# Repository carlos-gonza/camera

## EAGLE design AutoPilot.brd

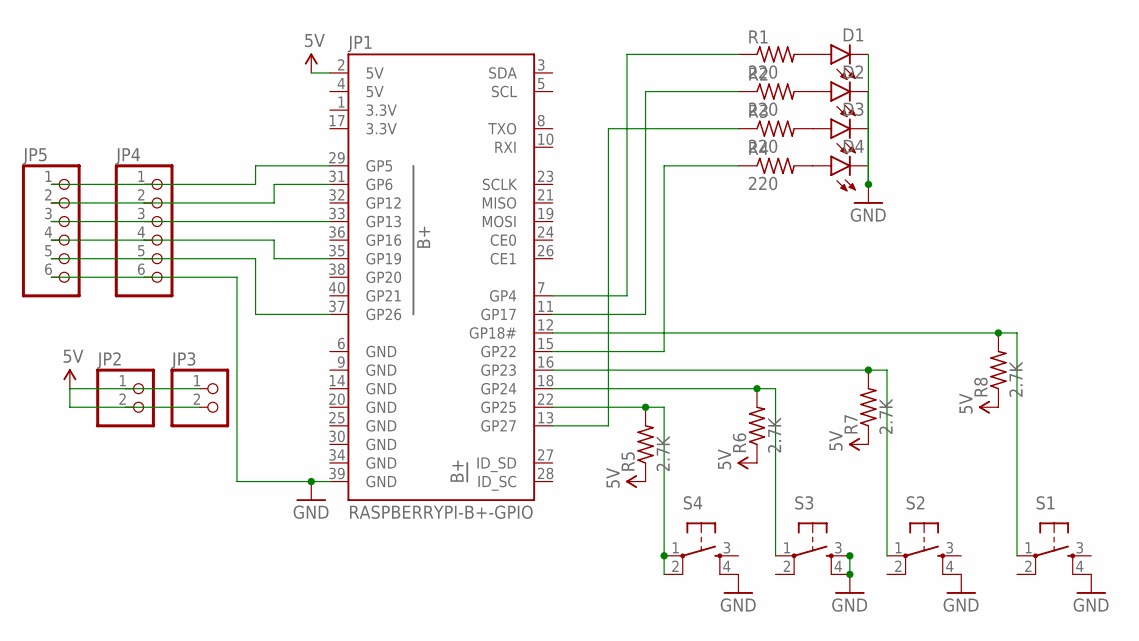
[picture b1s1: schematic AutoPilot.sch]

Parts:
D1, D2, D3, D4: LED5MM
JP1: RASPBERRYPI-B+-GPIO; 2X20-SHROUDED
JP2, JP3: PINHD-1X2; 1X02
JP4, JP5: PINHD-1X6; 1X06
R1, R2, R3, R4: 220; 0204V
R5, R6, R7, R8: 2.7K; 0204V
S1, S2, S3, S4: TAC_SWITCHPTH; TACTILE-PTH

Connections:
3.3V: JP1.1 (3.3V), JP1.17 (3.3V)
5V: JP1.2 (5V), JP1.4 (5V), JP2.1, JP2.2, JP3.1, JP3.2, R5.1, R6.1, R7.1, R8.1
GND: D1.K (C), D2.K (C), D3.K (C), D4.K (C), JP1.6 (GND), JP1.9 (GND), JP1.14 (GND), JP1.20 (GND), JP1.25 (GND), JP1.30 (GND), JP1.34 (GND), JP1.39 (GND), JP4.6, JP5.6, S1.4, S2.4, S3.3, S3.4, S4.4
unnamed: JP1.12 (GP18#), R8.2, S1.1
unnamed: JP1.7 (GP4), R1.1
unnamed: JP1.18 (GP24), R6.2, S3.1
unnamed: JP1.22 (GP25), R5.2, S4.1, S4.2
unnamed: JP1.29 (GP5), JP4.1, JP5.1
unnamed: JP1.31 (GP6), JP4.2, JP5.2
unnamed: D2.A, R2.2
unnamed: D3.A, R3.2
unnamed: D1.A, R1.2
unnamed: D4.A, R4.2
unnamed: JP1.16 (GP23), R7.2, S2.1
unnamed: JP1.11 (GP17), R2.1
unnamed: JP1.15 (GP22), R4.1
unnamed: JP1.13 (GP27), R3.1
unnamed: JP1.33 (GP13), JP4.3, JP5.3
unnamed: JP1.35 (GP19), JP4.4, JP5.4
unnamed: JP1.37 (GP26), JP4.5, JP5.5

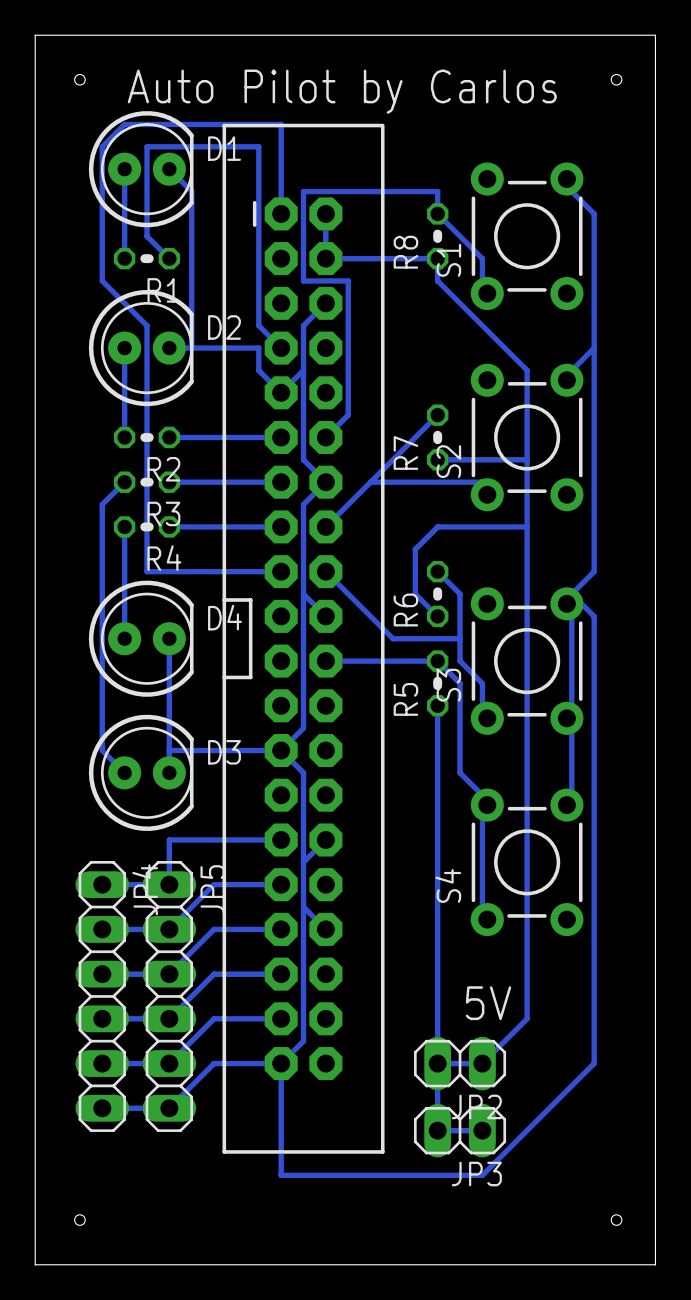
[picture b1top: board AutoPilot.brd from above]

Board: 2 copper layers, 35.2 x 69.8 mm, 21 parts (0 on the bottom side), 20 nets.

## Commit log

2017-01-05 raspberry pi project for lane drift technology

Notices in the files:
parts and their libraries:
SparkFun-Boards: Licensing: Creative Commons ShareAlike 4.0 International - https://creativecommons.org/licenses/by-sa/4.0
